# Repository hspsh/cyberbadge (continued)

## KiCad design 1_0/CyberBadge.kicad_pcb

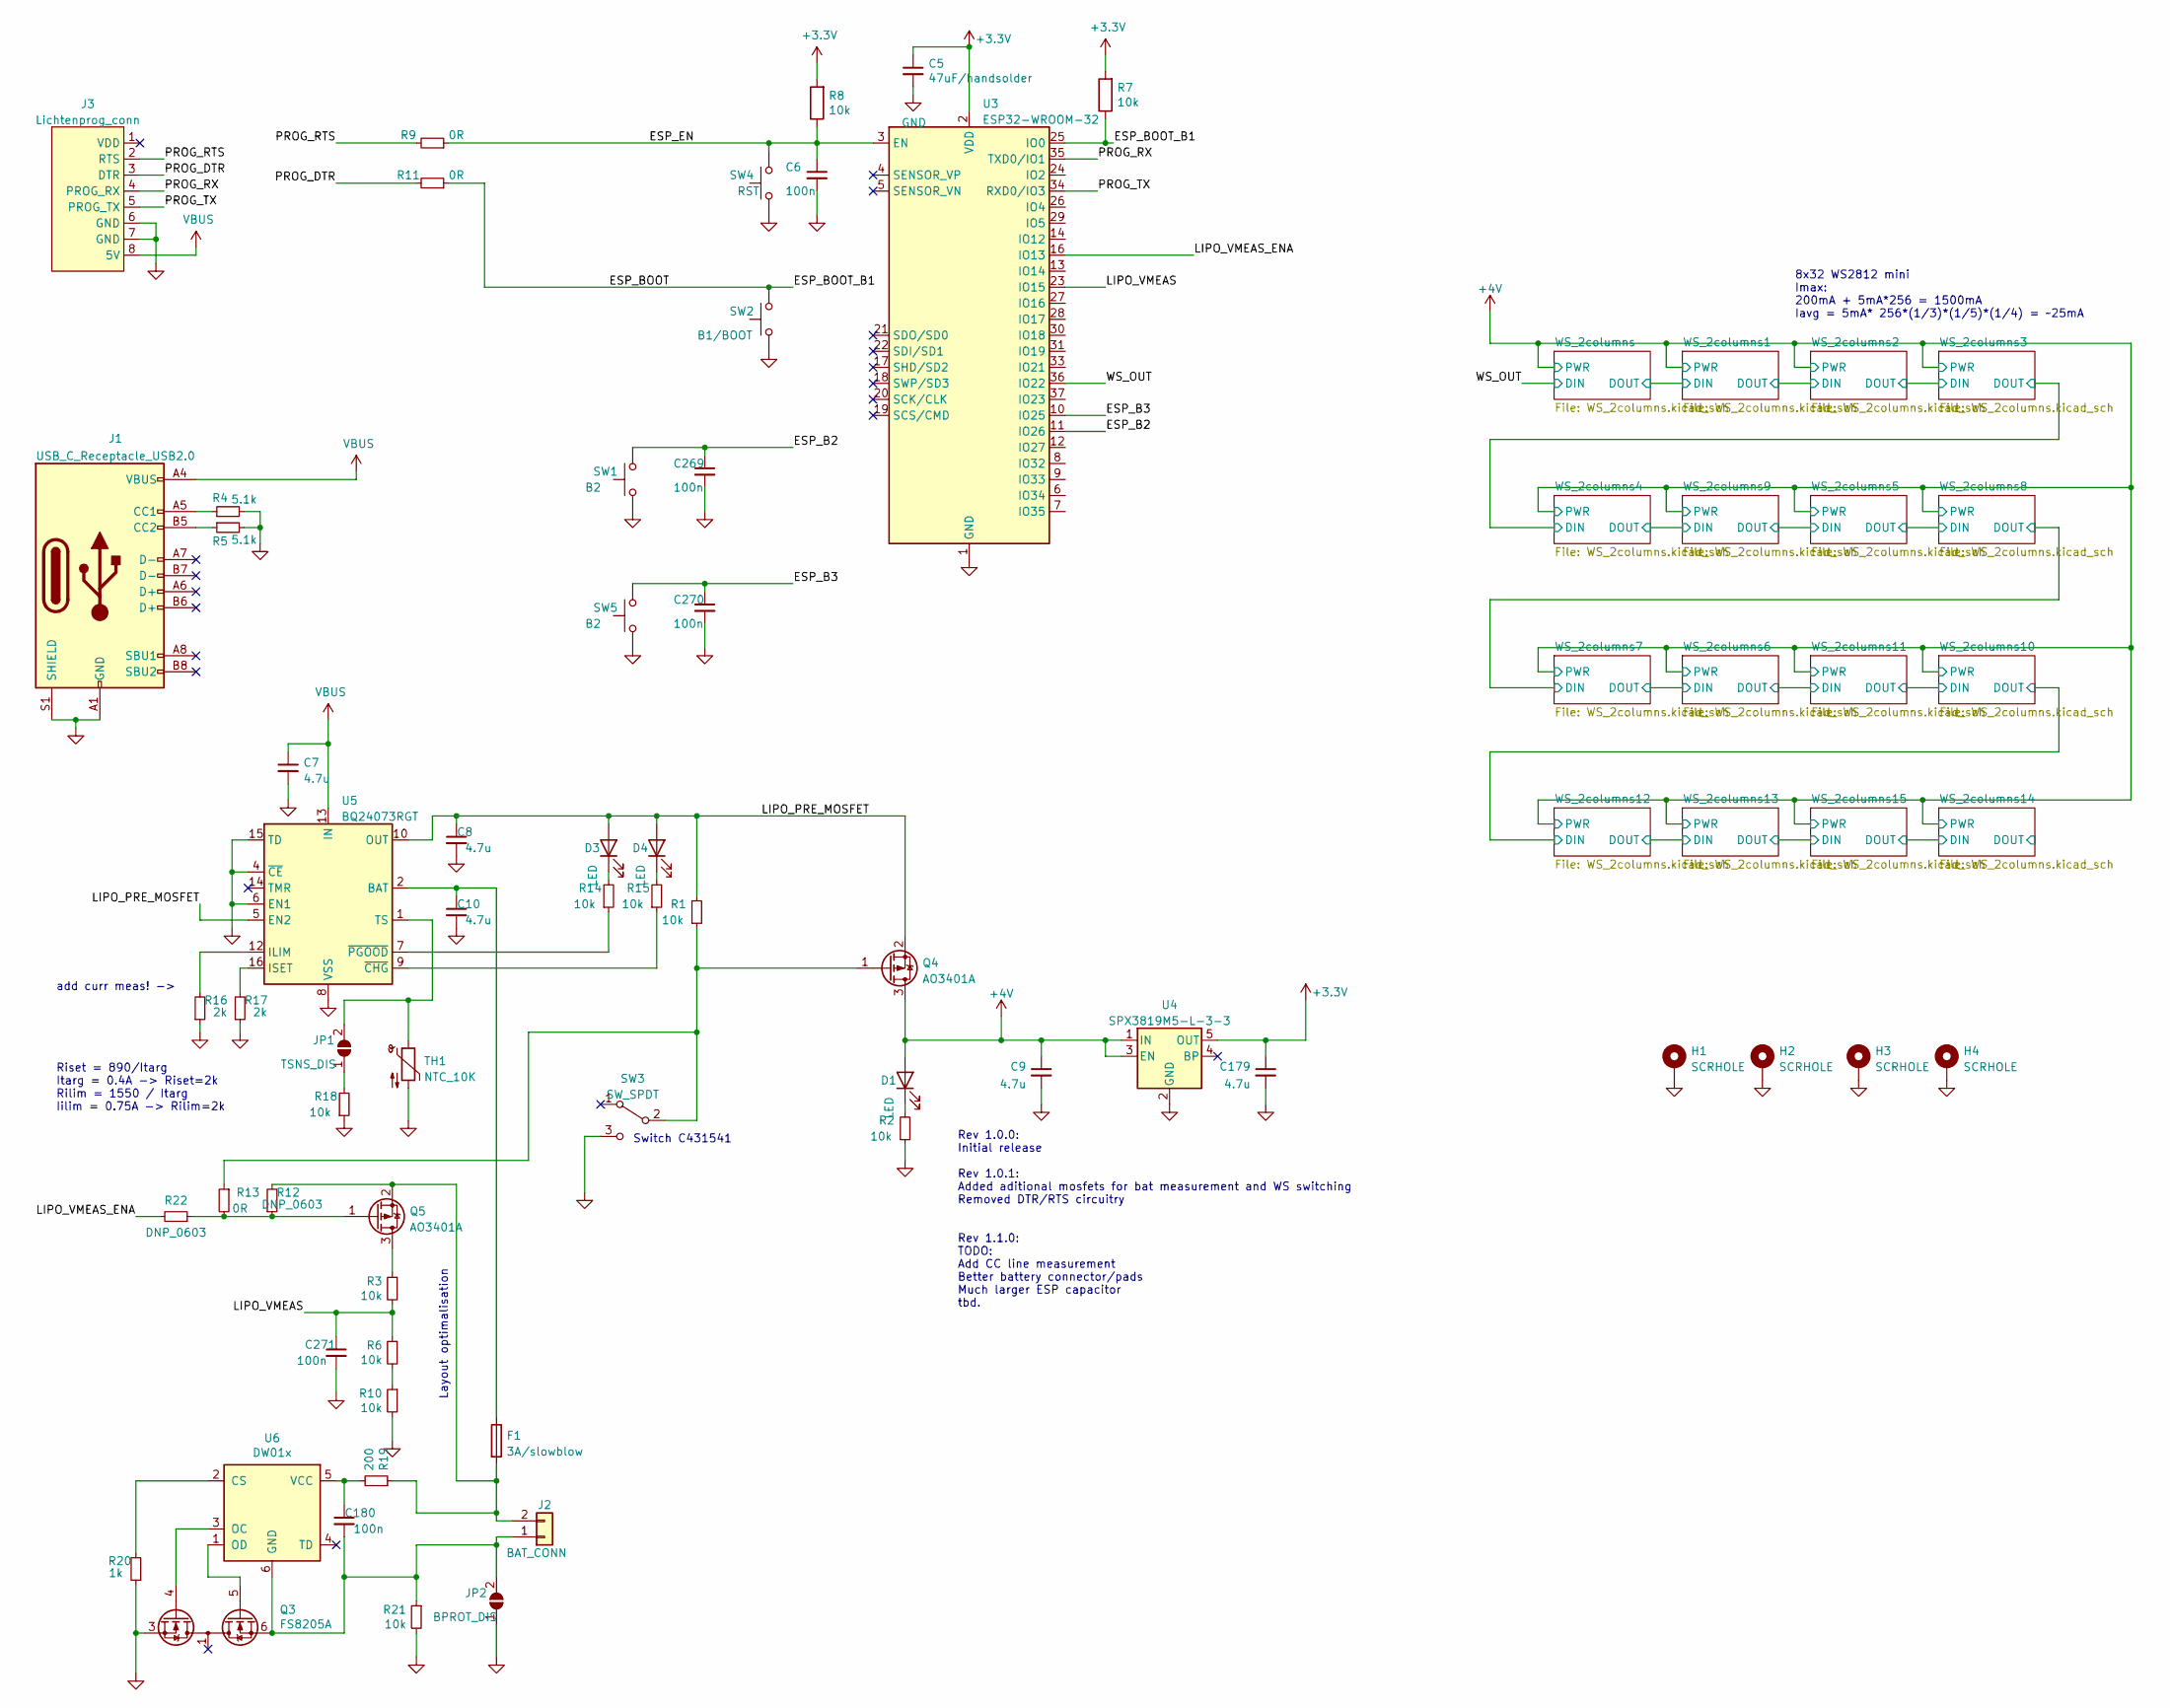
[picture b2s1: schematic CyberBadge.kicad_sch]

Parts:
C5: 47uF/handsolder; C_1210_3225Metric_Pad1.33x2.70mm_HandSolder
C6, C180, C269, C270, C271: 100n; C_0201_0603Metric
C7, C8, C9, C10, C179: 4.7u; C_0402_1005Metric; LCSC C19702
D1, D3, D4: LED; LED_0603_1608Metric
F1: 3A/slowblow; Fuse_0603_1608Metric_Pad1.05x0.95mm_HandSolder
H1, H2, H3, H4: SCRHOLE; MountingHole_3.2mm_M3
J1: USB_C_Receptacle_USB2.0; USB_C_Receptacle_HRO_TYPE-C-31-M-12; LCSC C165948
J2: BAT_CONN; JST_PH_S2B-PH-K_1x02_P2.00mm_Horizontal
J3: Lichtenprog_conn; Lichtenprog
JP1: TSNS_DIS; SolderJumper-2_P1.3mm_Open_TrianglePad1.0x1.5mm
JP2: BPROT_DIS; SolderJumper-2_P1.3mm_Open_TrianglePad1.0x1.5mm
Q3: FS8205A; TSSOP-8_4.4x3mm_P0.65mm
Q4, Q5: AO3401A; SOT-23
R1, R2, R3, R6, R10, R14, R15, R18, R21: 10k; R_0201_0603Metric; LCSC C25768
R4, R5: 5.1k; R_0201_0603Metric; LCSC C25117
R7, R8: 10k; R_0201_0603Metric
R9, R11, R13: 0R; R_0603_1608Metric_Pad0.98x0.95mm_HandSolder; LCSC C25117
R12, R22: DNP_0603; R_0603_1608Metric_Pad0.98x0.95mm_HandSolder; LCSC C25117
R16, R17: 2k; R_0603_1608Metric_Pad0.98x0.95mm_HandSolder; LCSC C25117
R19: 200; R_0201_0603Metric; LCSC C25768
R20: 1k; R_0201_0603Metric; LCSC C25117
SW1, SW5: B2; SW_SPST_TL3342
SW2: B1/BOOT; SW_SPST_TL3342
SW3: SW_SPDT; SW_SPDT_PCM12
SW4: RST; SW_SPST_FSMSM
TH1: NTC_10K; TestPoint_2Pads_Pitch2.54mm_Drill0.8mm
U3: ESP32-WROOM-32
U4: SPX3819M5-L-3-3; SOT-23-5
U5: BQ24073RGT; VQFN-16-1EP_3x3mm_P0.5mm_EP1.6x1.6mm_ThermalVias
U6: DW01x; SOT-23-6

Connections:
+3.3V: C5.1, C179.1, R7.2, R8.2, U3.2 (VDD), U4.5 (OUT)
+4V: C9.1, D1.2 (A), Q4.3 (D), U4.1 (IN), U4.3 (EN); also elsewhere on the board
/ESP_B2: C269.1, SW1.2, U3.11 (IO26)
/ESP_B3: C270.1, SW5.2, U3.10 (IO25)
/ESP_BOOT: R7.1, R11.1, SW2.2, U3.25 (IO0)
/ESP_EN: C6.1, R8.1, R9.1, SW4.2, U3.3 (EN)
/LIPO_PRE_MOSFET: C8.1, D3.2 (A), D4.2 (A), Q4.2 (S), R1.2, U5.5 (EN2), U5.10 (OUT), U5.11 (OUT)
/LIPO_VMEAS: C271.1, R3.2, R6.1, U3.23 (IO15)
/LIPO_VMEAS_ENA: R22.2, U3.16 (IO13)
/PROG_DTR: J3.3 (DTR), R11.2
/PROG_RTS: J3.2 (RTS), R9.2
/PROG_RX: J3.4 (PROG_RX), U3.35 (TXD0/IO1)
/PROG_TX: J3.5 (PROG_TX), U3.34 (RXD0/IO3)
/WS_OUT: U3.36 (IO22); also elsewhere on the board
GND: C5.2, C6.2, C7.2, C8.2, C9.2, C10.2, C179.2, C269.2, C270.2, C271.2, H1.1, H2.1, H3.1, H4.1, J1.A1 (GND), J1.A12 (GND), J1.B1 (GND), J1.B12 (GND), J1.S1 (SHIELD), J3.6 (GND), J3.7 (GND), JP2.1 (A), Q3.2 (S1), Q3.3 (S1), R2.1, R4.2, R5.2, R10.2, R16.1, R17.1, R18.1, R20.1, R21.2, SW1.1, SW2.1, SW3.3 (C), SW4.1, SW5.1, TH1.2, U3.1 (GND), U3.15 (GND), U3.38 (GND), U3.39 (GND), U4.2 (GND), U5.4 (~CE), U5.6 (EN1), U5.8 (VSS), U5.15 (TD), U5.17 (VSS); also elsewhere on the board
unnamed: C10.1, F1.1, U5.2 (BAT), U5.3 (BAT)
unnamed: D1.1 (K), R2.2
unnamed: D3.1 (K), R14.2
unnamed: D4.1 (K), R15.2
unnamed: J1.A5 (CC1), R4.1
unnamed: J1.B5 (CC2), R5.1
unnamed: C180.2, J2.1, JP2.2 (B), Q3.6 (S2), Q3.7 (S2), R21.1, U6.6 (GND)
unnamed: F1.2, J2.2, Q5.2 (S), R12.2, R19.1
unnamed: JP1.1 (A), R18.2
unnamed: JP1.2 (B), TH1.1, U5.1 (TS)
unnamed: Q3.4 (G1), U6.3 (OC)
unnamed: Q3.5 (G2), U6.1 (OD)
unnamed: Q4.1 (G), R1.1, R13.1, SW3.2 (B)
unnamed: Q5.3 (D), R3.1
unnamed: Q5.1 (G), R12.1, R13.2, R22.1
unnamed: R6.2, R10.1
unnamed: R16.2, U5.12 (ILIM)
unnamed: R17.2, U5.16 (ISET)
unnamed: R15.1, U5.9 (~CHG)
unnamed: R14.1, U5.7 (~PGOOD)
unnamed: R20.2, U6.2 (CS)
unnamed: C180.1, R19.2, U6.5 (VCC)
VBUS: C7.1, J1.A4 (VBUS), J1.A9 (VBUS), J1.B4 (VBUS), J1.B9 (VBUS), J3.8 (5V), U5.13 (IN)

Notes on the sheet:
Switch C431541
Riset = 890/Itarg Itarg = 0.4A -> Riset=2k Rilim = 1550 / Itarg Iilim = 0.75A -> Rilim=2k
8x32 WS2812 mini Imax: 200mA + 5mA*256 = 1500mA Iavg = 5mA* 256*(1/3)*(1/5)*(1/4) = ~25mA
Layout optimalisation
add curr meas! ->
Rev 1.0.0: Initial release Rev 1.0.1: Added aditional mosfets for bat measurement and WS switching Removed DTR/RTS circuitry Rev 1.1.0: TODO: Add CC line measurement Better battery connector/pads Much larger ESP capacitor tbd.

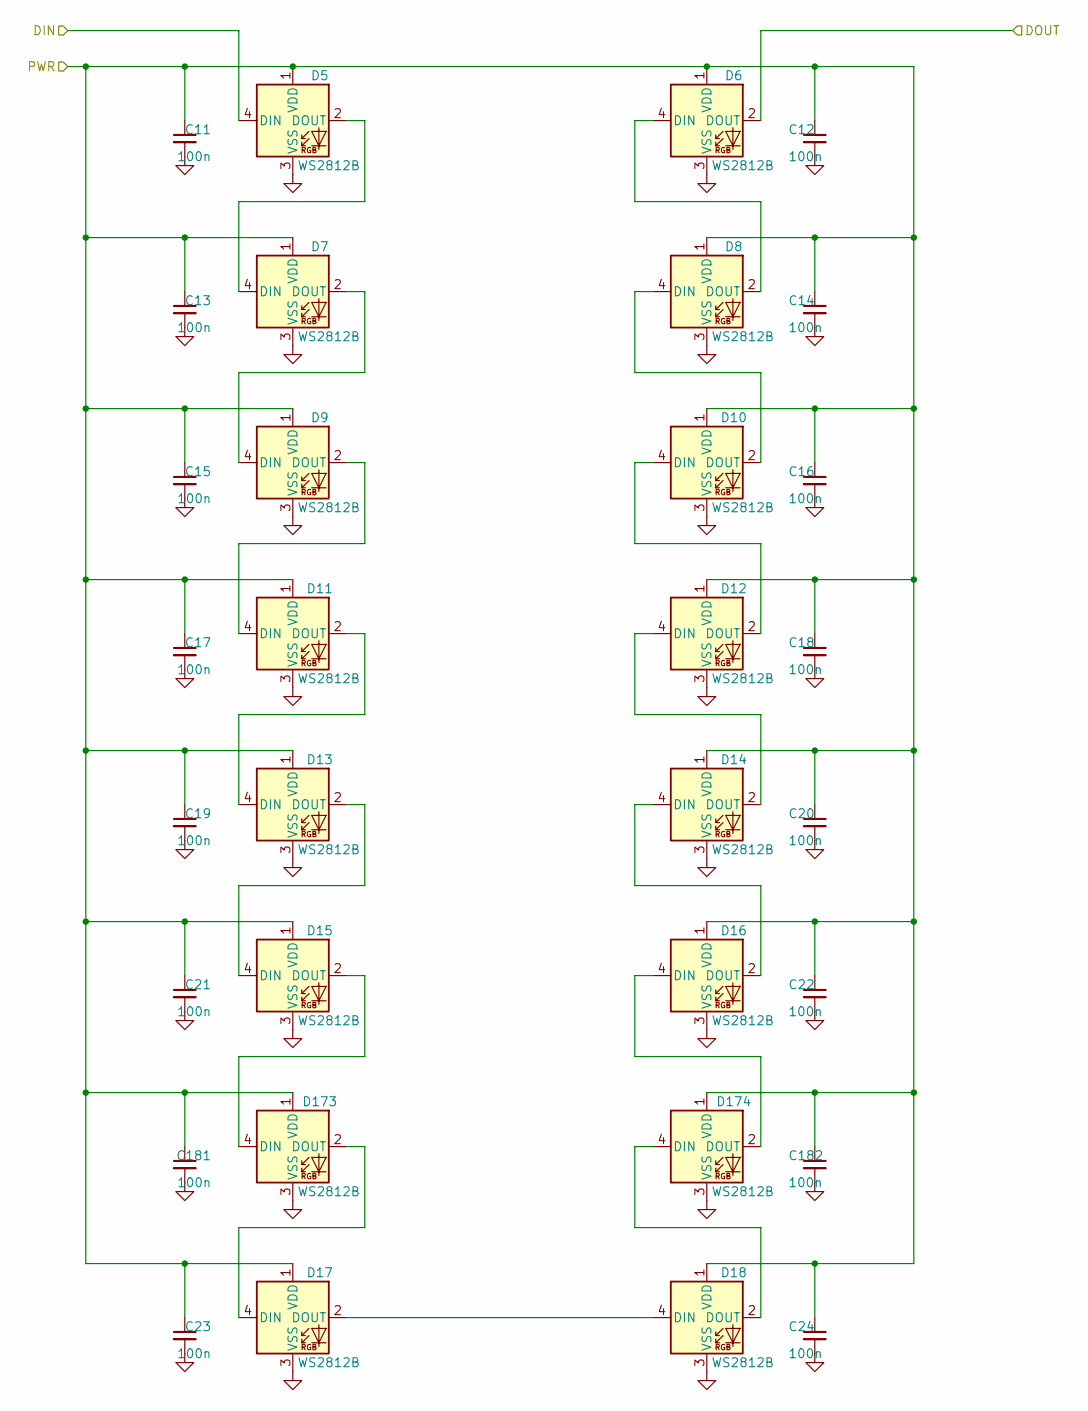
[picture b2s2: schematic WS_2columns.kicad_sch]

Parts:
C11, C12, C13, C14, C15, C16, C17, C18, C19, C20, C21, C22, C23, C24, C181, C182: 100n; C_0201_0603Metric
D5, D6, D7, D8, D9, D10, D11, D12, D13, D14, D15, D16, D17, D18, D173, D174: WS2812B; LED_WS2812B-2020_pinsRenumbered

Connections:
+4V: C11.1, C12.1, C13.1, C14.1, C15.1, C16.1, C17.1, C18.1, C19.1, C20.1, C21.1, C22.1, C23.1, C24.1, C181.1, C182.1, D5.1 (VDD), D6.1 (VDD), D7.1 (VDD), D8.1 (VDD), D9.1 (VDD), D10.1 (VDD), D11.1 (VDD), D12.1 (VDD), D13.1 (VDD), D14.1 (VDD), D15.1 (VDD), D16.1 (VDD), D17.1 (VDD), D18.1 (VDD), D173.1 (VDD), D174.1 (VDD); also elsewhere on the board
/WS_2columns/DOUT: D6.2 (DOUT); also elsewhere on the board
/WS_OUT: D5.4 (DIN); also elsewhere on the board
GND: C11.2, C12.2, C13.2, C14.2, C15.2, C16.2, C17.2, C18.2, C19.2, C20.2, C21.2, C22.2, C23.2, C24.2, C181.2, C182.2, D5.3 (VSS), D6.3 (VSS), D7.3 (VSS), D8.3 (VSS), D9.3 (VSS), D10.3 (VSS), D11.3 (VSS), D12.3 (VSS), D13.3 (VSS), D14.3 (VSS), D15.3 (VSS), D16.3 (VSS), D17.3 (VSS), D18.3 (VSS), D173.3 (VSS), D174.3 (VSS); also elsewhere on the board
unnamed: D5.2 (DOUT), D7.4 (DIN)
unnamed: D6.4 (DIN), D8.2 (DOUT)
unnamed: D7.2 (DOUT), D9.4 (DIN)
unnamed: D10.4 (DIN), D12.2 (DOUT)
unnamed: D8.4 (DIN), D10.2 (DOUT)
unnamed: D9.2 (DOUT), D11.4 (DIN)
unnamed: D11.2 (DOUT), D13.4 (DIN)
unnamed: D12.4 (DIN), D14.2 (DOUT)
unnamed: D13.2 (DOUT), D15.4 (DIN)
unnamed: D14.4 (DIN), D16.2 (DOUT)
unnamed: D15.2 (DOUT), D173.4 (DIN)
unnamed: D16.4 (DIN), D174.2 (DOUT)
unnamed: D17.4 (DIN), D173.2 (DOUT)
unnamed: D17.2 (DOUT), D18.4 (DIN)
unnamed: D18.2 (DOUT), D174.4 (DIN)

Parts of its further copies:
C25, C26, C27, C28, C29, C30, C31, C32, C33, C34, C35, C36, C37, C38, C39, C40, C41, C42, C43, C44, C45, C46, C47, C48, C49, C50, C51, C52, C53, C54, C55, C56, C57, C58, C59, C60, C61, C62, C63, C64, C65, C66, C67, C68, C69, C70, C71, C72, C73, C74, C75, C76, C77, C78, C79, C80, C81, C82, C83, C84, C85, C86, C87, C88, C89, C90, C91, C92, C93, C94, C95, C96, C97, C98, C99, C100, C101, C102, C103, C104, C105, C106, C107, C108, C109, C110, C111, C112, C113, C114, C115, C116, C117, C118, C119, C120, C121, C122, C123, C124, C125, C126, C127, C128, C129, C130, C131, C132, C133, C134, C135, C136, C137, C138, C139, C140, C141, C142, C143, C144, C145, C146, C147, C148, C149, C150, C151, C152, C153, C154, C155, C156, C157, C158, C159, C160, C161, C162, C163, C164, C165, C166, C167, C168, C169, C170, C171, C172, C173, C174, C175, C176, C177, C178, C183, C184, C185, C186, C187, C188, C189, C190, C191, C192, C193, C194, C195, C196, C197, C198, C199, C200, C201, C202, C203, C204, C205, C206, C207, C208, C209, C210, C211, C212, C213, C214, C215, C216, C217, C218, C219, C220, C221, C222, C223, C224, C225, C226, C227, C228, C229, C230, C231, C232, C233, C234, C235, C236, C237, C238, C239, C240, C241, C242, C243, C244, C245, C246, C247, C248, C249, C250, C251, C252, C253, C254, C255, C256, C257, C258, C259, C260, C261, C262, C263, C264, C265, C266, C267, C268: 100n; C_0201_0603Metric
D19, D20, D21, D22, D23, D24, D25, D26, D27, D28, D29, D30, D31, D32, D33, D34, D35, D36, D37, D38, D39, D40, D41, D42, D43, D44, D45, D46, D47, D48, D49, D50, D51, D52, D53, D54, D55, D56, D57, D58, D59, D60, D61, D62, D63, D64, D65, D66, D67, D68, D69, D70, D71, D72, D73, D74, D75, D76, D77, D78, D79, D80, D81, D82, D83, D84, D85, D86, D87, D88, D89, D90, D91, D92, D93, D94, D95, D96, D97, D98, D99, D100, D101, D102, D103, D104, D105, D106, D107, D108, D109, D110, D111, D112, D113, D114, D115, D116, D117, D118, D119, D120, D121, D122, D123, D124, D125, D126, D127, D128, D129, D130, D131, D132, D133, D134, D135, D136, D137, D138, D139, D140, D141, D142, D143, D144, D145, D146, D147, D148, D149, D150, D151, D152, D153, D154, D155, D156, D157, D158, D159, D160, D161, D162, D163, D164, D165, D166, D167, D168, D169, D170, D171, D172, D175, D176, D177, D178, D179, D180, D181, D182, D183, D184, D185, D186, D187, D188, D189, D190, D191, D192, D193, D194, D195, D196, D197, D198, D199, D200, D201, D202, D203, D204, D205, D206, D207, D208, D209, D210, D211, D212, D213, D214, D215, D216, D217, D218, D219, D220, D221, D222, D223, D224, D225, D226, D227, D228, D229, D230, D231, D232, D233, D234, D235, D236, D237, D238, D239, D240, D241, D242, D243, D244, D245, D246, D247, D248, D249, D250, D251, D252, D253, D254, D255, D256, D257, D258, D259, D260: WS2812B; LED_WS2812B-2020_pinsRenumbered

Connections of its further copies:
+4V: C25.1, C26.1, C27.1, C28.1, C29.1, C30.1, C31.1, C32.1, C33.1, C34.1, C35.1, C36.1, C37.1, C38.1, C39.1, C40.1, C41.1, C42.1, C43.1, C44.1, C45.1, C46.1, C47.1, C48.1, C49.1, C50.1, C51.1, C52.1, C53.1, C54.1, C55.1, C56.1, C57.1, C58.1, C59.1, C60.1, C61.1, C62.1, C63.1, C64.1, C65.1, C66.1, C67.1, C68.1, C69.1, C70.1, C71.1, C72.1, C73.1, C74.1, C75.1, C76.1, C77.1, C78.1, C79.1, C80.1, C81.1, C82.1, C83.1, C84.1, C85.1, C86.1, C87.1, C88.1, C89.1, C90.1, C91.1, C92.1, C93.1, C94.1, C95.1, C96.1, C97.1, C98.1, C99.1, C100.1, C101.1, C102.1, C103.1, C104.1, C105.1, C106.1, C107.1, C108.1, C109.1, C110.1, C111.1, C112.1, C113.1, C114.1, C115.1, C116.1, C117.1, C118.1, C119.1, C120.1, C121.1, C122.1, C123.1, C124.1, C125.1, C126.1, C127.1, C128.1, C129.1, C130.1, C131.1, C132.1, C133.1, C134.1, C135.1, C136.1, C137.1, C138.1, C139.1, C140.1, C141.1, C142.1, C143.1, C144.1, C145.1, C146.1, C147.1, C148.1, C149.1, C150.1, C151.1, C152.1, C153.1, C154.1, C155.1, C156.1, C157.1, C158.1, C159.1, C160.1, C161.1, C162.1, C163.1, C164.1, C165.1, C166.1, C167.1, C168.1, C169.1, C170.1, C171.1, C172.1, C173.1, C174.1, C175.1, C176.1, C177.1, C178.1, C183.1, C184.1, C185.1, C186.1, C187.1, C188.1, C189.1, C190.1, C191.1, C192.1, C193.1, C194.1, C195.1, C196.1, C197.1, C198.1, C199.1, C200.1, C201.1, C202.1, C203.1, C204.1, C205.1, C206.1, C207.1, C208.1, C209.1, C210.1, C211.1, C212.1, C213.1, C214.1, C215.1, C216.1, C217.1, C218.1, C219.1, C220.1, C221.1, C222.1, C223.1, C224.1, C225.1, C226.1, C227.1, C228.1, C229.1, C230.1, C231.1, C232.1, C233.1, C234.1, C235.1, C236.1, C237.1, C238.1, C239.1, C240.1, C241.1, C242.1, C243.1, C244.1, C245.1, C246.1, C247.1, C248.1, C249.1, C250.1, C251.1, C252.1, C253.1, C254.1, C255.1, C256.1, C257.1, C258.1, C259.1, C260.1, C261.1, C262.1, C263.1, C264.1, C265.1, C266.1, C267.1, C268.1, D19.1 (VDD), D20.1 (VDD), D21.1 (VDD), D22.1 (VDD), D23.1 (VDD), D24.1 (VDD), D25.1 (VDD), D26.1 (VDD), D27.1 (VDD), D28.1 (VDD), D29.1 (VDD), D30.1 (VDD), D31.1 (VDD), D32.1 (VDD), D33.1 (VDD), D34.1 (VDD), D35.1 (VDD), D36.1 (VDD), D37.1 (VDD), D38.1 (VDD), D39.1 (VDD), D40.1 (VDD), D41.1 (VDD), D42.1 (VDD), D43.1 (VDD), D44.1 (VDD), D45.1 (VDD), D46.1 (VDD), D47.1 (VDD), D48.1 (VDD), D49.1 (VDD), D50.1 (VDD), D51.1 (VDD), D52.1 (VDD), D53.1 (VDD), D54.1 (VDD), D55.1 (VDD), D56.1 (VDD), D57.1 (VDD), D58.1 (VDD), D59.1 (VDD), D60.1 (VDD), D61.1 (VDD), D62.1 (VDD), D63.1 (VDD), D64.1 (VDD), D65.1 (VDD), D66.1 (VDD), D67.1 (VDD), D68.1 (VDD), D69.1 (VDD), D70.1 (VDD), D71.1 (VDD), D72.1 (VDD), D73.1 (VDD), D74.1 (VDD), D75.1 (VDD), D76.1 (VDD), D77.1 (VDD), D78.1 (VDD), D79.1 (VDD), D80.1 (VDD), D81.1 (VDD), D82.1 (VDD), D83.1 (VDD), D84.1 (VDD), D85.1 (VDD), D86.1 (VDD), D87.1 (VDD), D88.1 (VDD), D89.1 (VDD), D90.1 (VDD), D91.1 (VDD), D92.1 (VDD), D93.1 (VDD), D94.1 (VDD), D95.1 (VDD), D96.1 (VDD), D97.1 (VDD), D98.1 (VDD), D99.1 (VDD), D100.1 (VDD), D101.1 (VDD), D102.1 (VDD), D103.1 (VDD), D104.1 (VDD), D105.1 (VDD), D106.1 (VDD), D107.1 (VDD), D108.1 (VDD), D109.1 (VDD), D110.1 (VDD), D111.1 (VDD), D112.1 (VDD), D113.1 (VDD), D114.1 (VDD), D115.1 (VDD), D116.1 (VDD), D117.1 (VDD), D118.1 (VDD), D119.1 (VDD), D120.1 (VDD), D121.1 (VDD), D122.1 (VDD), D123.1 (VDD), D124.1 (VDD), D125.1 (VDD), D126.1 (VDD), D127.1 (VDD), D128.1 (VDD), D129.1 (VDD), D130.1 (VDD), D131.1 (VDD), D132.1 (VDD), D133.1 (VDD), D134.1 (VDD), D135.1 (VDD), D136.1 (VDD), D137.1 (VDD), D138.1 (VDD), D139.1 (VDD), D140.1 (VDD), D141.1 (VDD), D142.1 (VDD), D143.1 (VDD), D144.1 (VDD), D145.1 (VDD), D146.1 (VDD), D147.1 (VDD), D148.1 (VDD), D149.1 (VDD), D150.1 (VDD), D151.1 (VDD), D152.1 (VDD), D153.1 (VDD), D154.1 (VDD), D155.1 (VDD), D156.1 (VDD), D157.1 (VDD), D158.1 (VDD), D159.1 (VDD), D160.1 (VDD), D161.1 (VDD), D162.1 (VDD), D163.1 (VDD), D164.1 (VDD), D165.1 (VDD), D166.1 (VDD), D167.1 (VDD), D168.1 (VDD), D169.1 (VDD), D170.1 (VDD), D171.1 (VDD), D172.1 (VDD), D175.1 (VDD), D176.1 (VDD), D177.1 (VDD), D178.1 (VDD), D179.1 (VDD), D180.1 (VDD), D181.1 (VDD), D182.1 (VDD), D183.1 (VDD), D184.1 (VDD), D185.1 (VDD), D186.1 (VDD), D187.1 (VDD), D188.1 (VDD), D189.1 (VDD), D190.1 (VDD), D191.1 (VDD), D192.1 (VDD), D193.1 (VDD), D194.1 (VDD), D195.1 (VDD), D196.1 (VDD), D197.1 (VDD), D198.1 (VDD), D199.1 (VDD), D200.1 (VDD), D201.1 (VDD), D202.1 (VDD), D203.1 (VDD), D204.1 (VDD), D205.1 (VDD), D206.1 (VDD), D207.1 (VDD), D208.1 (VDD), D209.1 (VDD), D210.1 (VDD), D211.1 (VDD), D212.1 (VDD), D213.1 (VDD), D214.1 (VDD), D215.1 (VDD), D216.1 (VDD), D217.1 (VDD), D218.1 (VDD), D219.1 (VDD), D220.1 (VDD), D221.1 (VDD), D222.1 (VDD), D223.1 (VDD), D224.1 (VDD), D225.1 (VDD), D226.1 (VDD), D227.1 (VDD), D228.1 (VDD), D229.1 (VDD), D230.1 (VDD), D231.1 (VDD), D232.1 (VDD), D233.1 (VDD), D234.1 (VDD)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; also elsewhere on the board
/WS_2columns1/DOUT: D20.2 (DOUT), D33.4 (DIN)
/WS_2columns2/DOUT: D34.2 (DOUT), D47.4 (DIN)
/WS_2columns3/DOUT: D48.2 (DOUT), D61.4 (DIN)
/WS_2columns4/DOUT: D62.2 (DOUT), D75.4 (DIN)
/WS_2columns5/DIN: D76.2 (DOUT), D89.4 (DIN)
/WS_2columns5/DOUT: D90.2 (DOUT), D103.4 (DIN)
/WS_2columns6/DIN: D118.2 (DOUT), D131.4 (DIN)
/WS_2columns7/DIN: D104.2 (DOUT), D117.4 (DIN)
/WS_2columns10/DIN: D146.2 (DOUT), D159.4 (DIN)
/WS_2columns10/DOUT: D160.2 (DOUT), D197.4 (DIN)
/WS_2columns11/DIN: D132.2 (DOUT), D145.4 (DIN)
/WS_2columns12/DOUT: D198.2 (DOUT), D213.4 (DIN)
/WS_2columns13/DOUT: D214.2 (DOUT), D229.4 (DIN)
/WS_2columns14/DIN: D230.2 (DOUT), D245.4 (DIN)
/WS_2columns14/DOUT: D246.2 (DOUT)
/WS_2columns/DOUT: D19.4 (DIN); also elsewhere on the board
GND: C25.2, C26.2, C27.2, C28.2, C29.2, C30.2, C31.2, C32.2, C33.2, C34.2, C35.2, C36.2, C37.2, C38.2, C39.2, C40.2, C41.2, C42.2, C43.2, C44.2, C45.2, C46.2, C47.2, C48.2, C49.2, C50.2, C51.2, C52.2, C53.2, C54.2, C55.2, C56.2, C57.2, C58.2, C59.2, C60.2, C61.2, C62.2, C63.2, C64.2, C65.2, C66.2, C67.2, C68.2, C69.2, C70.2, C71.2, C72.2, C73.2, C74.2, C75.2, C76.2, C77.2, C78.2, C79.2, C80.2, C81.2, C82.2, C83.2, C84.2, C85.2, C86.2, C87.2, C88.2, C89.2, C90.2, C91.2, C92.2, C93.2, C94.2, C95.2, C96.2, C97.2, C98.2, C99.2, C100.2, C101.2, C102.2, C103.2, C104.2, C105.2, C106.2, C107.2, C108.2, C109.2, C110.2, C111.2, C112.2, C113.2, C114.2, C115.2, C116.2, C117.2, C118.2, C119.2, C120.2, C121.2, C122.2, C123.2, C124.2, C125.2, C126.2, C127.2, C128.2, C129.2, C130.2, C131.2, C132.2, C133.2, C134.2, C135.2, C136.2, C137.2, C138.2, C139.2, C140.2, C141.2, C142.2, C143.2, C144.2, C145.2, C146.2, C147.2, C148.2, C149.2, C150.2, C151.2, C152.2, C153.2, C154.2, C155.2, C156.2, C157.2, C158.2, C159.2, C160.2, C161.2, C162.2, C163.2, C164.2, C165.2, C166.2, C167.2, C168.2, C169.2, C170.2, C171.2, C172.2, C173.2, C174.2, C175.2, C176.2, C177.2, C178.2, C183.2, C184.2, C185.2, C186.2, C187.2, C188.2, C189.2, C190.2, C191.2, C192.2, C193.2, C194.2, C195.2, C196.2, C197.2, C198.2, C199.2, C200.2, C201.2, C202.2, C203.2, C204.2, C205.2, C206.2, C207.2, C208.2, C209.2, C210.2, C211.2, C212.2, C213.2, C214.2, C215.2, C216.2, C217.2, C218.2, C219.2, C220.2, C221.2, C222.2, C223.2, C224.2, C225.2, C226.2, C227.2, C228.2, C229.2, C230.2, C231.2, C232.2, C233.2, C234.2, C235.2, C236.2, C237.2, C238.2, C239.2, C240.2, C241.2, C242.2, C243.2, C244.2, C245.2, C246.2, C247.2, C248.2, C249.2, C250.2, C251.2, C252.2, C253.2, C254.2, C255.2, C256.2, C257.2, C258.2, C259.2, C260.2, C261.2, C262.2, C263.2, C264.2, C265.2, C266.2, C267.2, C268.2, D19.3 (VSS), D20.3 (VSS), D21.3 (VSS), D22.3 (VSS), D23.3 (VSS), D24.3 (VSS), D25.3 (VSS), D26.3 (VSS), D27.3 (VSS), D28.3 (VSS), D29.3 (VSS), D30.3 (VSS), D31.3 (VSS), D32.3 (VSS), D33.3 (VSS), D34.3 (VSS), D35.3 (VSS), D36.3 (VSS), D37.3 (VSS), D38.3 (VSS), D39.3 (VSS), D40.3 (VSS), D41.3 (VSS), D42.3 (VSS), D43.3 (VSS), D44.3 (VSS), D45.3 (VSS), D46.3 (VSS), D47.3 (VSS), D48.3 (VSS), D49.3 (VSS), D50.3 (VSS), D51.3 (VSS), D52.3 (VSS), D53.3 (VSS), D54.3 (VSS), D55.3 (VSS), D56.3 (VSS), D57.3 (VSS), D58.3 (VSS), D59.3 (VSS), D60.3 (VSS), D61.3 (VSS), D62.3 (VSS), D63.3 (VSS), D64.3 (VSS), D65.3 (VSS), D66.3 (VSS), D67.3 (VSS), D68.3 (VSS), D69.3 (VSS), D70.3 (VSS), D71.3 (VSS), D72.3 (VSS), D73.3 (VSS), D74.3 (VSS), D75.3 (VSS), D76.3 (VSS), D77.3 (VSS), D78.3 (VSS), D79.3 (VSS), D80.3 (VSS), D81.3 (VSS), D82.3 (VSS), D83.3 (VSS), D84.3 (VSS), D85.3 (VSS), D86.3 (VSS), D87.3 (VSS), D88.3 (VSS), D89.3 (VSS), D90.3 (VSS), D91.3 (VSS), D92.3 (VSS), D93.3 (VSS), D94.3 (VSS), D95.3 (VSS), D96.3 (VSS), D97.3 (VSS), D98.3 (VSS), D99.3 (VSS), D100.3 (VSS), D101.3 (VSS), D102.3 (VSS), D103.3 (VSS), D104.3 (VSS), D105.3 (VSS), D106.3 (VSS), D107.3 (VSS), D108.3 (VSS), D109.3 (VSS), D110.3 (VSS), D111.3 (VSS), D112.3 (VSS), D113.3 (VSS), D114.3 (VSS), D115.3 (VSS), D116.3 (VSS), D117.3 (VSS), D118.3 (VSS), D119.3 (VSS), D120.3 (VSS), D121.3 (VSS), D122.3 (VSS), D123.3 (VSS), D124.3 (VSS), D125.3 (VSS), D126.3 (VSS), D127.3 (VSS), D128.3 (VSS), D129.3 (VSS), D130.3 (VSS), D131.3 (VSS), D132.3 (VSS), D133.3 (VSS), D134.3 (VSS), D135.3 (VSS), D136.3 (VSS), D137.3 (VSS), D138.3 (VSS), D139.3 (VSS), D140.3 (VSS), D141.3 (VSS), D142.3 (VSS), D143.3 (VSS), D144.3 (VSS), D145.3 (VSS), D146.3 (VSS), D147.3 (VSS), D148.3 (VSS), D149.3 (VSS), D150.3 (VSS), D151.3 (VSS), D152.3 (VSS), D153.3 (VSS), D154.3 (VSS), D155.3 (VSS), D156.3 (VSS), D157.3 (VSS), D158.3 (VSS), D159.3 (VSS), D160.3 (VSS), D161.3 (VSS), D162.3 (VSS), D163.3 (VSS), D164.3 (VSS), D165.3 (VSS), D166.3 (VSS), D167.3 (VSS), D168.3 (VSS), D169.3 (VSS), D170.3 (VSS), D171.3 (VSS), D172.3 (VSS), D175.3 (VSS), D176.3 (VSS), D177.3 (VSS), D178.3 (VSS), D179.3 (VSS), D180.3 (VSS), D181.3 (VSS), D182.3 (VSS), D183.3 (VSS), D184.3 (VSS), D185.3 (VSS), D186.3 (VSS), D187.3 (VSS), D188.3 (VSS), D189.3 (VSS), D190.3 (VSS), D191.3 (VSS), D192.3 (VSS), D193.3 (VSS), D194.3 (VSS), D195.3 (VSS), D196.3 (VSS), D197.3 (VSS), D198.3 (VSS), D199.3 (VSS), D200.3 (VSS), D201.3 (VSS), D202.3 (VSS), D203.3 (VSS), D204.3 (VSS), D205.3 (VSS), D206.3 (VSS), D207.3 (VSS), D208.3 (VSS), D209.3 (VSS), D210.3 (VSS), D211.3 (VSS), D212.3 (VSS), D213.3 (VSS), D214.3 (VSS), D215.3 (VSS), D216.3 (VSS), D217.3 (VSS), D218.3 (VSS), D219.3 (VSS), D220.3 (VSS), D221.3 (VSS), D222.3 (VSS), D223.3 (VSS), D224.3 (VSS), D225.3 (VSS), D226.3 (VSS), D227.3 (VSS), D228.3 (VSS), D229.3 (VSS), D230.3 (VSS), D231.3 (VSS), D232.3 (VSS), D233.3 (VSS), D234.3 (VSS)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; also elsewhere on the board
unnamed: D19.2 (DOUT), D21.4 (DIN)
unnamed: D20.4 (DIN), D22.2 (DOUT)
unnamed: D21.2 (DOUT), D23.4 (DIN)
unnamed: D22.4 (DIN), D24.2 (DOUT)
unnamed: D23.2 (DOUT), D25.4 (DIN)
unnamed: D24.4 (DIN), D26.2 (DOUT)
unnamed: D25.2 (DOUT), D27.4 (DIN)
unnamed: D26.4 (DIN), D28.2 (DOUT)
unnamed: D27.2 (DOUT), D29.4 (DIN)
unnamed: D28.4 (DIN), D30.2 (DOUT)
unnamed: D31.2 (DOUT), D32.4 (DIN)
unnamed: D33.2 (DOUT), D35.4 (DIN)
unnamed: D34.4 (DIN), D36.2 (DOUT)
unnamed: D35.2 (DOUT), D37.4 (DIN)
unnamed: D36.4 (DIN), D38.2 (DOUT)
unnamed: D37.2 (DOUT), D39.4 (DIN)
unnamed: D38.4 (DIN), D40.2 (DOUT)
unnamed: D39.2 (DOUT), D41.4 (DIN)
unnamed: D40.4 (DIN), D42.2 (DOUT)
unnamed: D41.2 (DOUT), D43.4 (DIN)
unnamed: D42.4 (DIN), D44.2 (DOUT)
unnamed: D45.2 (DOUT), D46.4 (DIN)
unnamed: D47.2 (DOUT), D49.4 (DIN)
unnamed: D48.4 (DIN), D50.2 (DOUT)
unnamed: D49.2 (DOUT), D51.4 (DIN)
unnamed: D50.4 (DIN), D52.2 (DOUT)
unnamed: D51.2 (DOUT), D53.4 (DIN)
unnamed: D52.4 (DIN), D54.2 (DOUT)
unnamed: D53.2 (DOUT), D55.4 (DIN)
unnamed: D54.4 (DIN), D56.2 (DOUT)
unnamed: D55.2 (DOUT), D57.4 (DIN)
unnamed: D56.4 (DIN), D58.2 (DOUT)
unnamed: D59.2 (DOUT), D60.4 (DIN)
unnamed: D61.2 (DOUT), D63.4 (DIN)
unnamed: D62.4 (DIN), D64.2 (DOUT)
unnamed: D63.2 (DOUT), D65.4 (DIN)
unnamed: D64.4 (DIN), D66.2 (DOUT)
unnamed: D65.2 (DOUT), D67.4 (DIN)
unnamed: D66.4 (DIN), D68.2 (DOUT)
unnamed: D67.2 (DOUT), D69.4 (DIN)
unnamed: D68.4 (DIN), D70.2 (DOUT)
unnamed: D69.2 (DOUT), D71.4 (DIN)
unnamed: D70.4 (DIN), D72.2 (DOUT)
unnamed: D73.2 (DOUT), D74.4 (DIN)
unnamed: D75.2 (DOUT), D77.4 (DIN)
unnamed: D76.4 (DIN), D78.2 (DOUT)
unnamed: D77.2 (DOUT), D79.4 (DIN)
unnamed: D78.4 (DIN), D80.2 (DOUT)
unnamed: D79.2 (DOUT), D81.4 (DIN)
unnamed: D80.4 (DIN), D82.2 (DOUT)
unnamed: D81.2 (DOUT), D83.4 (DIN)
unnamed: D82.4 (DIN), D84.2 (DOUT)
unnamed: D83.2 (DOUT), D85.4 (DIN)
unnamed: D84.4 (DIN), D86.2 (DOUT)
unnamed: D87.2 (DOUT), D88.4 (DIN)
unnamed: D89.2 (DOUT), D91.4 (DIN)
unnamed: D90.4 (DIN), D92.2 (DOUT)
unnamed: D91.2 (DOUT), D93.4 (DIN)
unnamed: D92.4 (DIN), D94.2 (DOUT)
unnamed: D93.2 (DOUT), D95.4 (DIN)
unnamed: D94.4 (DIN), D96.2 (DOUT)
unnamed: D95.2 (DOUT), D97.4 (DIN)
unnamed: D96.4 (DIN), D98.2 (DOUT)
unnamed: D97.2 (DOUT), D99.4 (DIN)
unnamed: D100.4 (DIN), D186.2 (DOUT)
unnamed: D98.4 (DIN), D100.2 (DOUT)
unnamed: D101.4 (DIN), D185.2 (DOUT)
unnamed: D101.2 (DOUT), D102.4 (DIN)
unnamed: D102.2 (DOUT), D186.4 (DIN)
unnamed: D103.2 (DOUT), D105.4 (DIN)
unnamed: D104.4 (DIN), D106.2 (DOUT)
unnamed: D105.2 (DOUT), D107.4 (DIN)
unnamed: D106.4 (DIN), D108.2 (DOUT)
unnamed: D107.2 (DOUT), D109.4 (DIN)
unnamed: D108.4 (DIN), D110.2 (DOUT)
unnamed: D109.2 (DOUT), D111.4 (DIN)
unnamed: D110.4 (DIN), D112.2 (DOUT)
unnamed: D111.2 (DOUT), D113.4 (DIN)
unnamed: D112.4 (DIN), D114.2 (DOUT)
unnamed: D113.2 (DOUT), D187.4 (DIN)
unnamed: D114.4 (DIN), D188.2 (DOUT)
unnamed: D115.4 (DIN), D187.2 (DOUT)
unnamed: D115.2 (DOUT), D116.4 (DIN)
unnamed: D116.2 (DOUT), D188.4 (DIN)
unnamed: D117.2 (DOUT), D119.4 (DIN)
unnamed: D118.4 (DIN), D120.2 (DOUT)
unnamed: D119.2 (DOUT), D121.4 (DIN)
unnamed: D120.4 (DIN), D122.2 (DOUT)
unnamed: D121.2 (DOUT), D123.4 (DIN)
unnamed: D122.4 (DIN), D124.2 (DOUT)
unnamed: D123.2 (DOUT), D125.4 (DIN)
unnamed: D124.4 (DIN), D126.2 (DOUT)
unnamed: D125.2 (DOUT), D127.4 (DIN)
unnamed: D126.4 (DIN), D128.2 (DOUT)
unnamed: D127.2 (DOUT), D189.4 (DIN)
unnamed: D128.4 (DIN), D190.2 (DOUT)
unnamed: D129.4 (DIN), D189.2 (DOUT)
unnamed: D129.2 (DOUT), D130.4 (DIN)
unnamed: D130.2 (DOUT), D190.4 (DIN)
unnamed: D131.2 (DOUT), D133.4 (DIN)
unnamed: D132.4 (DIN), D134.2 (DOUT)
unnamed: D133.2 (DOUT), D135.4 (DIN)
unnamed: D134.4 (DIN), D136.2 (DOUT)
unnamed: D135.2 (DOUT), D137.4 (DIN)
unnamed: D136.4 (DIN), D138.2 (DOUT)
unnamed: D137.2 (DOUT), D139.4 (DIN)
unnamed: D138.4 (DIN), D140.2 (DOUT)
unnamed: D139.2 (DOUT), D141.4 (DIN)
unnamed: D140.4 (DIN), D142.2 (DOUT)
unnamed: D141.2 (DOUT), D191.4 (DIN)
unnamed: D142.4 (DIN), D192.2 (DOUT)
unnamed: D143.4 (DIN), D191.2 (DOUT)
unnamed: D143.2 (DOUT), D144.4 (DIN)
unnamed: D144.2 (DOUT), D192.4 (DIN)
unnamed: D145.2 (DOUT), D147.4 (DIN)
unnamed: D146.4 (DIN), D148.2 (DOUT)
unnamed: D147.2 (DOUT), D149.4 (DIN)
unnamed: D148.4 (DIN), D150.2 (DOUT)
unnamed: D149.2 (DOUT), D151.4 (DIN)
unnamed: D150.4 (DIN), D152.2 (DOUT)
unnamed: D151.2 (DOUT), D153.4 (DIN)
unnamed: D152.4 (DIN), D154.2 (DOUT)
unnamed: D153.2 (DOUT), D155.4 (DIN)
unnamed: D154.4 (DIN), D156.2 (DOUT)
unnamed: D155.2 (DOUT), D193.4 (DIN)
unnamed: D156.4 (DIN), D194.2 (DOUT)
unnamed: D157.4 (DIN), D193.2 (DOUT)
unnamed: D157.2 (DOUT), D158.4 (DIN)
unnamed: D158.2 (DOUT), D194.4 (DIN)
unnamed: D159.2 (DOUT), D161.4 (DIN)
unnamed: D160.4 (DIN), D162.2 (DOUT)
unnamed: D161.2 (DOUT), D163.4 (DIN)
unnamed: D162.4 (DIN), D164.2 (DOUT)
unnamed: D163.2 (DOUT), D165.4 (DIN)
unnamed: D164.4 (DIN), D166.2 (DOUT)
unnamed: D165.2 (DOUT), D167.4 (DIN)
unnamed: D166.4 (DIN), D168.2 (DOUT)
unnamed: D167.2 (DOUT), D169.4 (DIN)
unnamed: D168.4 (DIN), D170.2 (DOUT)
unnamed: D169.2 (DOUT), D195.4 (DIN)
unnamed: D170.4 (DIN), D196.2 (DOUT)
unnamed: D171.4 (DIN), D195.2 (DOUT)
unnamed: D171.2 (DOUT), D172.4 (DIN)
unnamed: D172.2 (DOUT), D196.4 (DIN)
unnamed: D29.2 (DOUT), D175.4 (DIN)
unnamed: D31.4 (DIN), D175.2 (DOUT)
unnamed: D32.2 (DOUT), D176.4 (DIN)
unnamed: D30.4 (DIN), D176.2 (DOUT)
unnamed: D43.2 (DOUT), D177.4 (DIN)
unnamed: D45.4 (DIN), D177.2 (DOUT)
unnamed: D46.2 (DOUT), D178.4 (DIN)
unnamed: D44.4 (DIN), D178.2 (DOUT)
unnamed: D57.2 (DOUT), D179.4 (DIN)
unnamed: D59.4 (DIN), D179.2 (DOUT)
unnamed: D60.2 (DOUT), D180.4 (DIN)
unnamed: D58.4 (DIN), D180.2 (DOUT)
unnamed: D71.2 (DOUT), D181.4 (DIN)
unnamed: D73.4 (DIN), D181.2 (DOUT)
unnamed: D74.2 (DOUT), D182.4 (DIN)
unnamed: D72.4 (DIN), D182.2 (DOUT)
unnamed: D85.2 (DOUT), D183.4 (DIN)
unnamed: D87.4 (DIN), D183.2 (DOUT)
unnamed: D88.2 (DOUT), D184.4 (DIN)
unnamed: D86.4 (DIN), D184.2 (DOUT)
unnamed: D99.2 (DOUT), D185.4 (DIN)
unnamed: D197.2 (DOUT), D199.4 (DIN)
unnamed: D198.4 (DIN), D200.2 (DOUT)
unnamed: D199.2 (DOUT), D201.4 (DIN)
unnamed: D200.4 (DIN), D202.2 (DOUT)
unnamed: D201.2 (DOUT), D203.4 (DIN)
unnamed: D202.4 (DIN), D204.2 (DOUT)
unnamed: D203.2 (DOUT), D205.4 (DIN)
unnamed: D204.4 (DIN), D206.2 (DOUT)
unnamed: D205.2 (DOUT), D207.4 (DIN)
unnamed: D206.4 (DIN), D208.2 (DOUT)
unnamed: D207.2 (DOUT), D209.4 (DIN)
unnamed: D208.4 (DIN), D210.2 (DOUT)
unnamed: D209.2 (DOUT), D211.4 (DIN)
unnamed: D210.4 (DIN), D212.2 (DOUT)
unnamed: D211.2 (DOUT), D212.4 (DIN)
unnamed: D213.2 (DOUT), D215.4 (DIN)
unnamed: D214.4 (DIN), D216.2 (DOUT)
unnamed: D215.2 (DOUT), D217.4 (DIN)
unnamed: D216.4 (DIN), D218.2 (DOUT)
unnamed: D217.2 (DOUT), D219.4 (DIN)
unnamed: D218.4 (DIN), D220.2 (DOUT)
unnamed: D219.2 (DOUT), D221.4 (DIN)
unnamed: D220.4 (DIN), D222.2 (DOUT)
unnamed: D221.2 (DOUT), D223.4 (DIN)
unnamed: D222.4 (DIN), D224.2 (DOUT)
unnamed: D223.2 (DOUT), D225.4 (DIN)
unnamed: D224.4 (DIN), D226.2 (DOUT)
unnamed: D225.2 (DOUT), D227.4 (DIN)
unnamed: D226.4 (DIN), D228.2 (DOUT)
unnamed: D227.2 (DOUT), D228.4 (DIN)
unnamed: D229.2 (DOUT), D231.4 (DIN)
unnamed: D230.4 (DIN), D232.2 (DOUT)
unnamed: D231.2 (DOUT), D233.4 (DIN)
unnamed: D232.4 (DIN), D234.2 (DOUT)
unnamed: D233.2 (DOUT), D235.4 (DIN)
unnamed: D234.4 (DIN), D236.2 (DOUT)
unnamed: D235.2 (DOUT), D237.4 (DIN)
unnamed: D236.4 (DIN), D238.2 (DOUT)
unnamed: D237.2 (DOUT), D239.4 (DIN)
unnamed: D238.4 (DIN), D240.2 (DOUT)
unnamed: D239.2 (DOUT), D241.4 (DIN)
unnamed: D240.4 (DIN), D242.2 (DOUT)
unnamed: D241.2 (DOUT), D243.4 (DIN)
unnamed: D242.4 (DIN), D244.2 (DOUT)
unnamed: D243.2 (DOUT), D244.4 (DIN)
unnamed: D245.2 (DOUT), D247.4 (DIN)
unnamed: D246.4 (DIN), D248.2 (DOUT)
unnamed: D247.2 (DOUT), D249.4 (DIN)
unnamed: D248.4 (DIN), D250.2 (DOUT)
unnamed: D249.2 (DOUT), D251.4 (DIN)
unnamed: D250.4 (DIN), D252.2 (DOUT)
unnamed: D251.2 (DOUT), D253.4 (DIN)
unnamed: D252.4 (DIN), D254.2 (DOUT)
unnamed: D253.2 (DOUT), D255.4 (DIN)
unnamed: D254.4 (DIN), D256.2 (DOUT)
unnamed: D255.2 (DOUT), D257.4 (DIN)
unnamed: D256.4 (DIN), D258.2 (DOUT)
unnamed: D257.2 (DOUT), D259.4 (DIN)
unnamed: D258.4 (DIN), D260.2 (DOUT)
unnamed: D259.2 (DOUT), D260.4 (DIN)

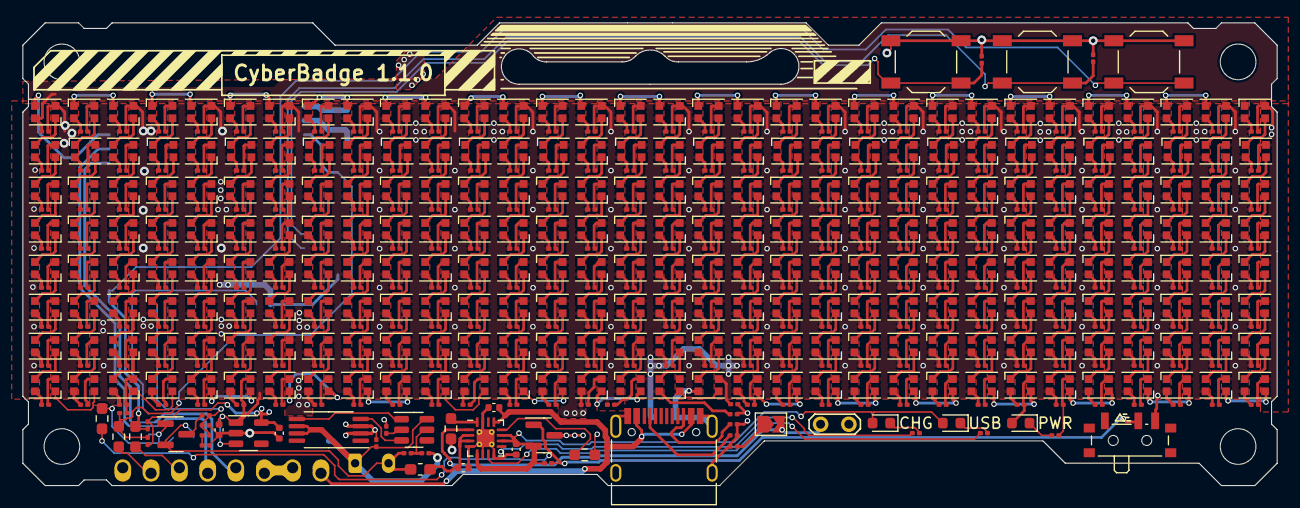
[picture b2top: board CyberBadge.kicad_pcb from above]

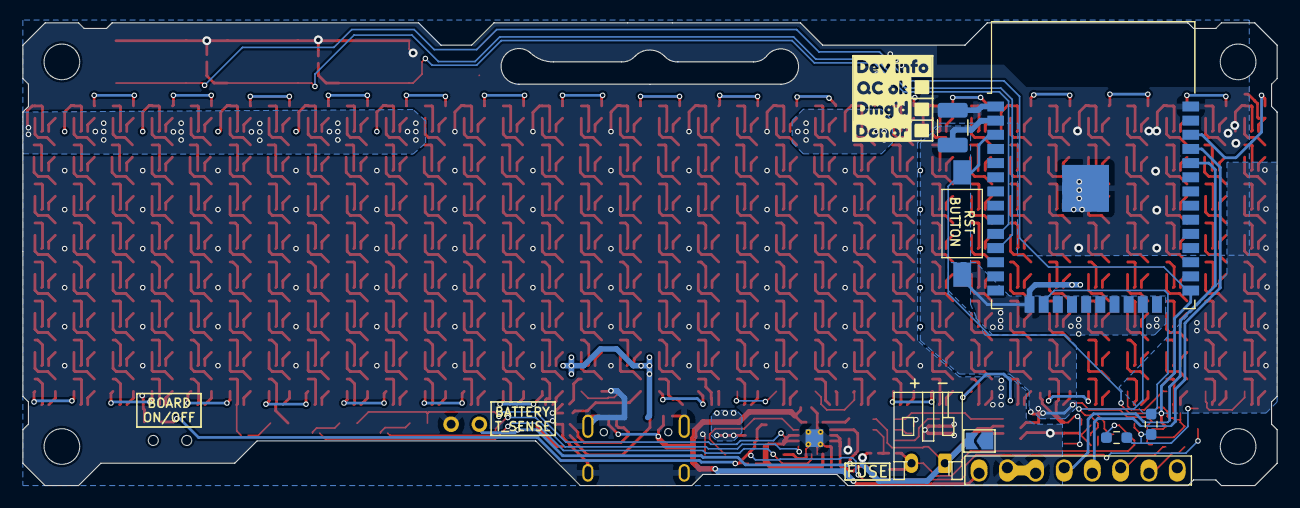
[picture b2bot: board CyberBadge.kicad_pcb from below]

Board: 2 copper layers, 112.5 x 41.5 mm, 575 parts (12 on the bottom side), 293 nets.

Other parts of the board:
kibuzzard-6394C46A: G***; kibuzzard-6394C46A
kibuzzard-6394C47E: G***; kibuzzard-6394C47E
kibuzzard-6394C445: G***; kibuzzard-6394C445
kibuzzard-6394C560: G***; kibuzzard-6394C560

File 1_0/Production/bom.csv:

Comment,Designator,Footprint,LCSC
47uF/handsolder,C5,Capacitor_SMD:C_1210_3225Metric_Pad1.33x2.70mm_HandSolder,C576521
100n,"C6,C11,C12,C13,C14,C15,C16,C17,C18,C19,C20,C21,C22,C23,C24,C25,C26,C27,C28,C29,C30,C31,C32,C33,C34,C35,C36,C37,C38,C39,C40,C41,C42,C43,C44,C45,C46,C47,C48,C49,C50,C51,C52,C53,C54,C55,C56,C57,C58,C59,C60,C61,C62,C63,C64,C65,C66,C67,C68,C69,C70,C71,C72,C73,C74,C75,C76,C77,C78,C79,C80,C81,C82,C83,C84,C85,C86,C87,C88,C89,C90,C91,C92,C93,C94,C95,C96,C97,C98,C99,C100,C101,C102,C103,C104,C105,C106,C107,C108,C109,C110,C111,C112,C113,C114,C115,C116,C117,C118,C119,C120,C121,C122,C123,C124,C125,C126,C127,C128,C129,C130,C131,C132,C133,C134,C135,C136,C137,C138,C139,C140,C141,C142,C143,C144,C145,C146,C147,C148,C149,C150,C151,C152,C153,C154,C155,C156,C157,C158,C159,C160,C161,C162,C163,C164,C165,C166,C167,C168,C169,C170,C171,C172,C173,C174,C175,C176,C177,C178,C180,C181,C182,C183,C184,C185,C186,C187,C188,C189,C190,C191,C192,C193,C194,C195,C196,C197,C198,C199,C200,C201,C202,C203,C204,C205,C206,C207,C208,C209,C210,C211,C212,C213,C214,C215,C216,C217,C218,C219,C220,C221,C222,C223,C224,C225,C226,C227,C228,C229,C230,C231,C232,C233,C234,C235,C236,C237,C238,C239,C240,C241,C242,C243,C244,C245,C246,C247,C248,C249,C250,C251,C252,C253,C254,C255,C256,C257,C258,C259,C260,C261,C262,C263,C264,C265,C266,C267,C268,C269,C270,C271",Capacitor_SMD:C_0201_0603Metric,C1525
4.7u,"C7,C8,C9,C10,C179",Capacitor_SMD:C_0402_1005Metric,C23733
LED,"D1,D3,D4",LED_SMD:LED_0603_1608Metric,C72038
WS2812B,"D5,D6,D7,D8,D9,D10,D11,D12,D13,D14,D15,D16,D17,D18,D19,D20,D21,D22,D23,D24,D25,D26,D27,D28,D29,D30,D31,D32,D33,D34,D35,D36,D37,D38,D39,D40,D41,D42,D43,D44,D45,D46,D47,D48,D49,D50,D51,D52,D53,D54,D55,D56,D57,D58,D59,D60,D61,D62,D63,D64,D65,D66,D67,D68,D69,D70,D71,D72,D73,D74,D75,D76,D77,D78,D79,D80,D81,D82,D83,D84,D85,D86,D87,D88,D89,D90,D91,D92,D93,D94,D95,D96,D97,D98,D99,D100,D101,D102,D103,D104,D105,D106,D107,D108,D109,D110,D111,D112,D113,D114,D115,D116,D117,D118,D119,D120,D121,D122,D123,D124,D125,D126,D127,D128,D129,D130,D131,D132,D133,D134,D135,D136,D137,D138,D139,D140,D141,D142,D143,D144,D145,D146,D147,D148,D149,D150,D151,D152,D153,D154,D155,D156,D157,D158,D159,D160,D161,D162,D163,D164,D165,D166,D167,D168,D169,D170,D171,D172,D173,D174,D175,D176,D177,D178,D179,D180,D181,D182,D183,D184,D185,D186,D187,D188,D189,D190,D191,D192,D193,D194,D195,D196,D197,D198,D199,D200,D201,D202,D203,D204,D205,D206,D207,D208,D209,D210,D211,D212,D213,D214,D215,D216,D217,D218,D219,D220,D221,D222,D223,D224,D225,D226,D227,D228,D229,D230,D231,D232,D233,D234,D235,D236,D237,D238,D239,D240,D241,D242,D243,D244,D245,D246,D247,D248,D249,D250,D251,D252,D253,D254,D255,D256,D257,D258,D259,D260",Critbit_lib:LED_WS2812B-2020_pinsRenumbered,C2976072
3A/slowblow,F1,Fuse:Fuse_0603_1608Metric_Pad1.05x0.95mm_HandSolder,C553913
USB_C_Receptacle_USB2.0,J1,Connector_USB:USB_C_Receptacle_HRO_TYPE-C-31-M-12,C165948
FS8205A,Q3,Package_SO:TSSOP-8_4.4x3mm_P0.65mm,C16052
AO3401A,"Q4,Q5",Package_TO_SOT_SMD:SOT-23,C15127
10k,"R1,R2,R3,R6,R7,R8,R10,R14,R15,R18,R21",Resistor_SMD:R_0201_0603Metric,C106225
2k,"R16,R17",Resistor_SMD:R_0603_1608Metric_Pad0.98x0.95mm_HandSolder,C22975
200,R19,Resistor_SMD:R_0201_0603Metric,C270359
1k,R20,Resistor_SMD:R_0201_0603Metric,C138165
5.1k,"R4,R5",Resistor_SMD:R_0201_0603Metric,C473460
0R,"R9,R11,R13",Resistor_SMD:R_0603_1608Metric_Pad0.98x0.95mm_HandSolder,C2889381
B2,"SW1,SW5",Button_Switch_SMD:SW_SPST_TL3342,C318884
B1/BOOT,SW2,Button_Switch_SMD:SW_SPST_TL3342,C318884
SW_SPDT,SW3,Button_Switch_SMD:SW_SPDT_PCM12,C431541
ESP32-WROOM-32,U3,RF_Module:ESP32-WROOM-32,C701342
SPX3819M5-L-3-3,U4,Package_TO_SOT_SMD:SOT-23-5,C9055
BQ24073RGT,U5,Package_DFN_QFN:VQFN-16-1EP_3x3mm_P0.5mm_EP1.6x1.6mm_ThermalVias,C15220
DW01x,U6,Package_TO_SOT_SMD:SOT-23-6,C351410

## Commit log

2022-11-26 add fiels
2023-01-03 some layout fiddling, but the schematic is not ready yet
2023-01-07 i forgor
2023-01-09 Add OpenSCAD project
2023-01-09 Add STL and 3MF
2023-01-09 Tweaks
2023-01-13 change pixel count
2023-01-15 commit before replicatelayout
2023-01-17 routing and shape definiton in progress
2023-01-19 add changes for review
2023-01-24 most of routing
2023-01-25 blah blah routing planes
2023-01-28 fix usb sw schematic, fix rev on silk
2023-01-29 routin sroutin, add bom
2023-01-30 add production stuff
2023-02-04 fix dumb bom
2023-02-18 outline
2023-02-19 Fitting diffuser
2023-02-26 schematic cleanup, add PDF and 3D model
2023-02-26 pin description in readme
2023-02-27 Add backcover
2023-02-27 backcover: Bigger strap hole
2023-03-11 Fat back
2023-03-13 Not sure how to track commit id in file
2023-04-11 add WIP
2023-04-17 move to kicad7, tweaks for second production run
2023-04-17 commit before editing project in notepad lmao
2023-05-08 Fix hook
2023-05-08 Git hook test
2023-05-08 Add funny script
2023-05-08 added pre-commit hook
2023-05-08 Huh, something stupid
2023-05-08 Increase button height
2023-05-08 Add new stl
2023-05-09 Forgor STL
2023-05-09 Notch
2023-05-11 Naklejka na skrzynke, ziom
2023-09-01 add files for 2.0
2023-09-01 wtf have i done
2023-09-01 cleanup 3d i guess
2023-11-25 2.0 FW poc
2024-01-02 put stuff for article etc.
2024-10-14 save before next rev
2024-10-15 commit before rescheme
2024-10-21 rescheme, reroute
2024-10-27 work on ledboard
2024-11-03 before oder
